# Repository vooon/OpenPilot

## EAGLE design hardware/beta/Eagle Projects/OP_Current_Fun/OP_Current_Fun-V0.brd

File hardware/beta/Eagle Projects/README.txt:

These are all easily accessible community projects, check schematic files for their usage licenses.

Extra or custom libraries are in lbr/Other.
OSH Park cam and DRU scripts are here as well.

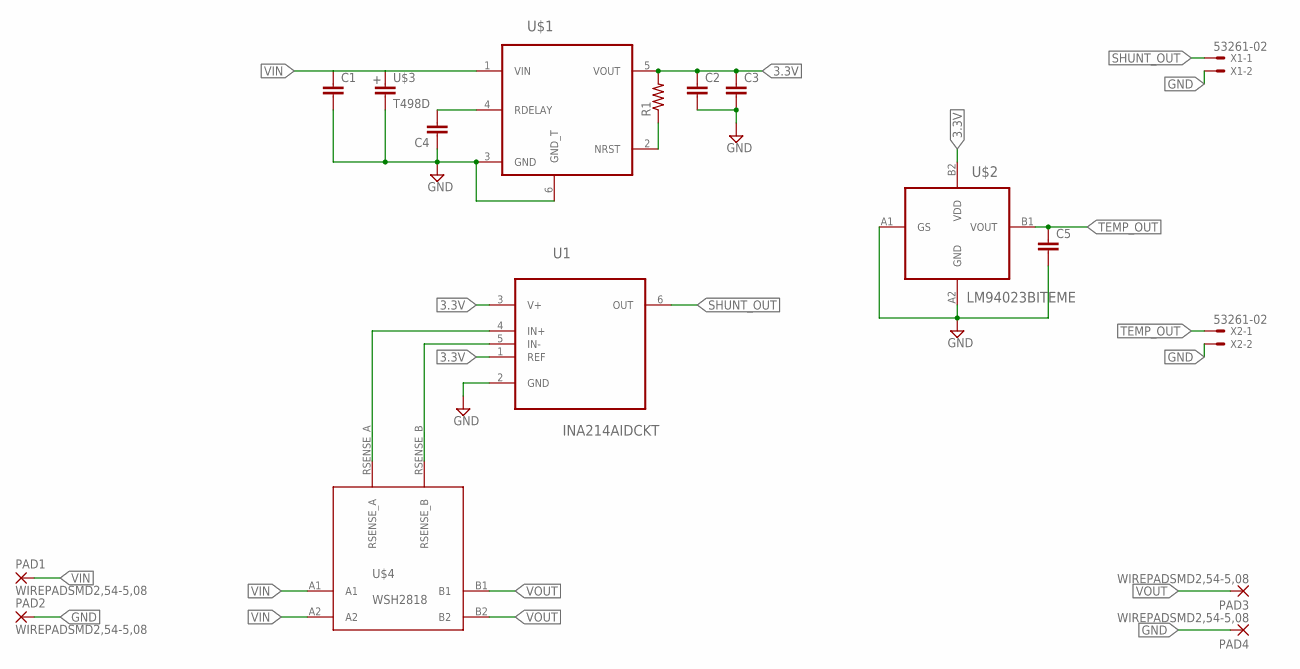
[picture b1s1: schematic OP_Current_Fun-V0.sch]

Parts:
C1, C2, C3, C5: C-EUC0603K; C0603K
C4: C-EUC0805K; C0805K
PAD1, PAD2, PAD3, PAD4: WIREPADSMD2,54-5,08; SMD2,54-5,08
R1: R-US_R0402; R0402
U1: INA214AIDCKT; SOT65P210X110-6N
U$1: TPS7A6033-Q1; TO-263-5
U$2: LM94023BITEME; BGA4C40P2X2_76X76X63
U$3: T498D; CT7343
U$4: WSH2818; 2818
X1, X2: 53261-02

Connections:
3.3V: C2.1, C3.1, R1.2, U1.1 (REF), U1.3 (V+), U$1.5 (VOUT), U$2.B2 (VDD)
GND: C1.2, C2.2, C3.2, C4.1, C5.2, PAD2.1, PAD4.1, U1.2 (GND), U$1.3 (GND), U$1.6 (GND_T), U$2.A1 (GS), U$2.A2 (GND), U$3.- (2), X1.2, X2.2
unnamed: U1.4 (IN+), U$4.RSENSE_A
unnamed: U1.5 (IN-), U$4.RSENSE_B
unnamed: C4.2, U$1.4 (RDELAY)
unnamed: R1.1, U$1.2 (NRST)
SHUNT_OUT: U1.6 (OUT), X1.1
TEMP_OUT: C5.1, U$2.B1 (VOUT), X2.1
VIN: C1.1, PAD1.1, U$1.1 (VIN), U$3.+ (1), U$4.A1, U$4.A2
VOUT: PAD3.1, U$4.B1, U$4.B2

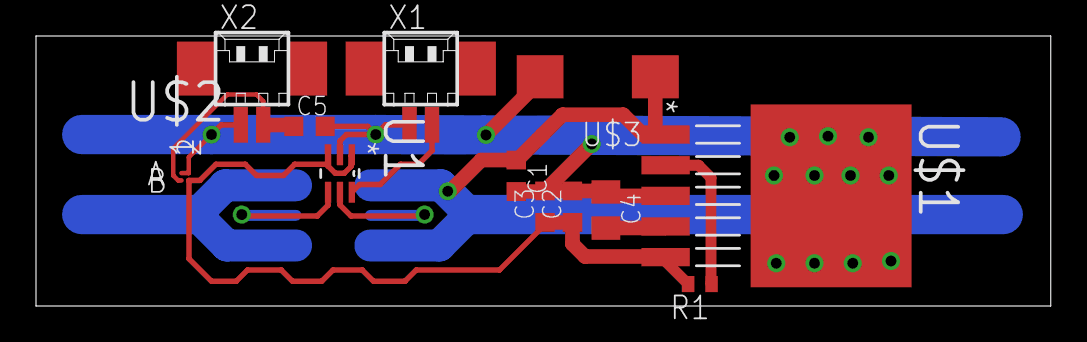
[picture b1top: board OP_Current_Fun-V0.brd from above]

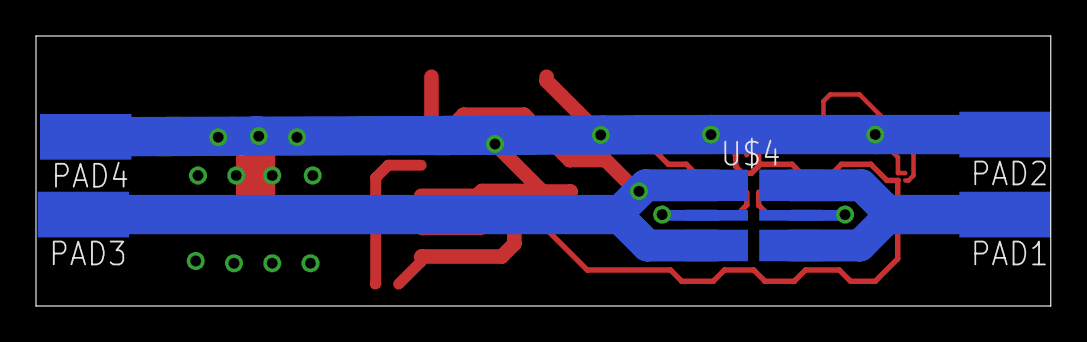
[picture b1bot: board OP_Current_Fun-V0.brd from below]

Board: 2 copper layers, 56.4 x 15.0 mm, 17 parts (5 on the bottom side), 10 nets.

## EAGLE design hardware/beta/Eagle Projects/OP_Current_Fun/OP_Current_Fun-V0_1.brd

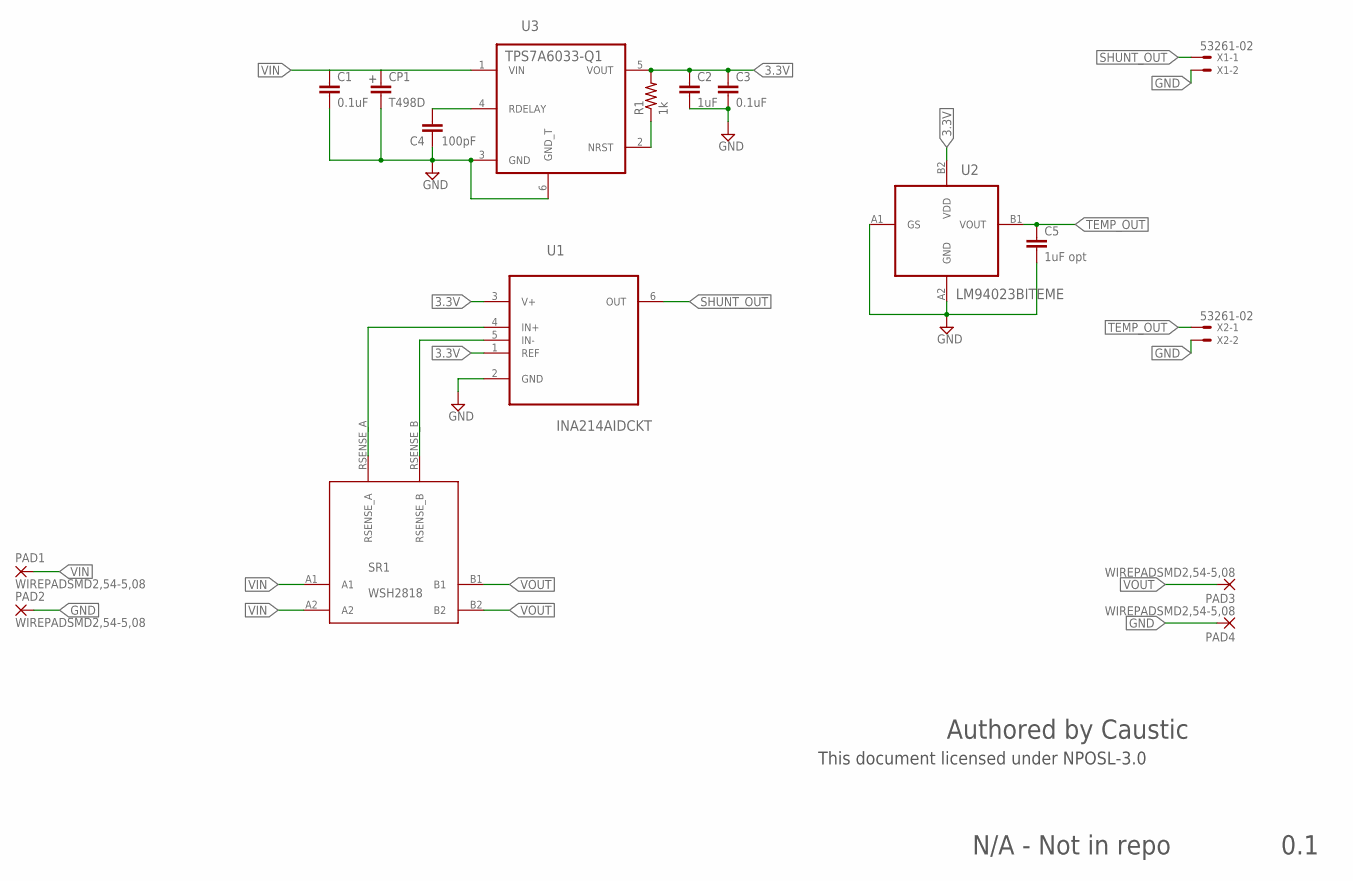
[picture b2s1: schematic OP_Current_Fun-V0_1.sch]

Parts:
C1, C3: 0.1uF; C0603K
C2: 1uF; C0603K
C4: 100pF; C0805K
C5: 1uF opt; C0603K
CP1: T498D; CT7343
PAD1, PAD2, PAD3, PAD4: WIREPADSMD2,54-5,08; SMD2,54-5,08
R1: 1k; R0402
SR1: WSH2818; 2818
U1: INA214AIDCKT; SOT65P210X110-6N
U2: LM94023BITEME; BGA4C40P2X2_76X76X63
U3: TPS7A6033-Q1; TO-263-5
X1, X2: 53261-02

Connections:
3.3V: C2.1, C3.1, R1.2, U1.1 (REF), U1.3 (V+), U2.B2 (VDD), U3.5 (VOUT)
GND: C1.2, C2.2, C3.2, C4.1, C5.2, CP1.- (2), PAD2.1, PAD4.1, U1.2 (GND), U2.A1 (GS), U2.A2 (GND), U3.3 (GND), U3.6 (GND_T), X1.2, X2.2
unnamed: SR1.RSENSE_A, U1.4 (IN+)
unnamed: SR1.RSENSE_B, U1.5 (IN-)
unnamed: C4.2, U3.4 (RDELAY)
unnamed: R1.1, U3.2 (NRST)
SHUNT_OUT: U1.6 (OUT), X1.1
TEMP_OUT: C5.1, U2.B1 (VOUT), X2.1
VIN: C1.1, CP1.+ (1), PAD1.1, SR1.A1, SR1.A2, U3.1 (VIN)
VOUT: PAD3.1, SR1.B1, SR1.B2

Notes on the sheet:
0.1
N/A - Not in repo
Authored by Caustic
This document licensed under NPOSL-3.0

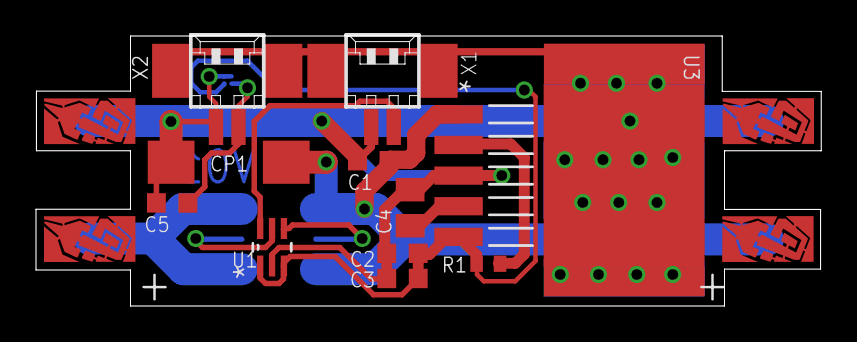
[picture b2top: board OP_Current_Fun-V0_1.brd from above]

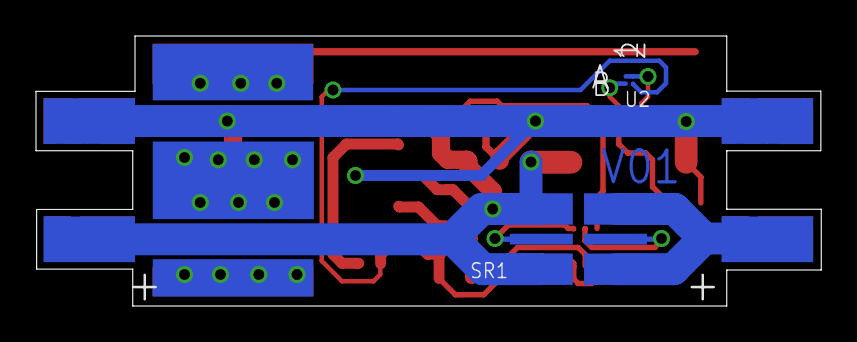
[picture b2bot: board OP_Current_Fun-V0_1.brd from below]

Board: 2 copper layers, 43.6 x 15.0 mm, 21 parts (6 on the bottom side), 10 nets.

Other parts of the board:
U$1, U$2, U$3, U$4: LOGO2,54X5,08PAD

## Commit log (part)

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2013-01-22 Added polarssl config include file.
2013-01-22 Fixed git submodule command.
2013-01-27 Added attitude direct control mode
    Attidude direct control mode is a regular pid control loop
    controlling a channel output to achieve an attitude. It works
    just like the Attutude mode except it is not a cascade controller.
    This is beneficial for controlling vehicles with reduced control over
    roll/pitch/yaw so that the cascade loop no longer makes sense (ie become
    impossible to tune)
2013-02-08 + added native Signals library
2013-02-08 + added classes: CApplication, CFile, CIODevice
2013-02-10 +added class: CStringList
2013-02-10 +added class CVariant
2013-02-21 Hitl fixes
2013-02-23 QT 5.0.1 *bugfixes *fix rawhid win event
2013-03-03 Updated arm toolchain filename. Updated to OP hosting URL (for 32bit).
2013-03-04 Copy over inc from CopterControl
2013-03-05 Copy coptercontrol main.c over
2013-03-05 Small Makefile comment to self
2013-03-05 Added CCUniversal to Makefile so we can try to build the bootloader
2013-03-05 Copied over board hw defs
2013-03-05 Created the External Library folder and readme.
2013-03-05 Stripped down the Standard Periph Libraries, do not need examples
2013-03-05 Start of MCU specific breakout and test, successful build
2013-03-06 Most of the versioned std lib works. The stdlib in PiOS is a different version, will have to patch or detect to maintain compatibility.
2013-03-07 Removed struct consts from bard_hw_defs
2013-03-07 Removed const from pios_board for led_cfg
2013-03-07 Removed const from first part of pios_usb
2013-03-08 Note to self about code duplication
2013-03-08 Updated F103 board file to versioned stdPeriphLib
2013-03-08 PiOS_led_priv converted to preprocessor test
2013-03-08 Converted PiOS_board to preprocessor test
2013-03-08 Added the filename stub needed to deal with the StdPeriphLib irregularity. Now builds as it should.
2013-03-08 Updated TESTNAME to pull in the F30x board file
2013-03-08 Copied over linker files, seem to match
2013-03-13 Added OP_Current_Fun and associated Eagle elements
2013-03-17 Remove discontinued AHRS files
2013-03-17 pios: common PIOS header guards
2013-03-17 pios: STM32F10x PIOS #ifdef guards
2013-03-17 Makefile: indents, comments, spacing, $(CMDS) variables, etc.
    How to invoke external command instead of shell builtin on Windows:
    ECHO := /bin/echo
2013-03-17 Makefile: use exported variables in firmware-defs.mk
    Note that $(QUOTE) variable is uppercased. Windows make does not
    export lowercased variables with export keyword (even if must do).
2013-03-17 Makefile: firmware makefiles cleanup (CC)
2013-03-17 Makefile: fix some MODULE_Name_BUILTIN checks and Makefile
    These names are automatically generated by make using the list
    of mandatory (always started) modules. Wrong names mean they can
    be disabled, fixed now.
2013-03-17 Makefile and pios_config.h cleanup for PipXtreme
    Now PipXtreme uses the same apps-defs.mk file as CopterControl.
    Next steps are F4 boards.
2013-03-17 Remove (almost) exact copy of dosfs from F1-specific directory
    The difference was in dfs_sdcard.c, line 107:
    -if((status = PIOS_SDCARD_SectorRead(sector, buffer)) < 0) {
    +if((status = PIOS_SDCARD_SectorRead(sector, buffer)) != 0) {
    Currenly unused, kept as is.
2013-03-17 Makefile: add --warn-common and --fatal-warnings to identify name clashes
    This will stop builds if few same symbols are found when linking.
    It should not be the case, but possible and may give unpredicted results.
2013-03-17 Remove duplicated global var and defines from board definition file
    Was caught using just added linker options:
    LDFLAGS += -Wl,--warn-common
    LDFLAGS += -Wl,--fatal-warnings
2013-03-17 pios_debug: use PIOS_INCLUDE_DEBUG_CONSOLE to DEBUG_PRINTF(level, ...)
    Inconsistent use of debug macros in board definition files resulted in
    BU compilation error. It was attempted to use PIOS_COM_SendFormattedStringNonBlocking()
    directly even if PIOS_COM was not included (like for BootloaderUpdater).
    So this function in pios_debug.c was replaced by DEBUG_PRINTF() macro.
    The macro itself is defined in pios_debug.h file. Its definitions are
    removed from board files. And to use it one has to define in pios_config.h:
2013-03-17 Remove never used op_config.h files (all occurences were empty)
2013-03-17 pios: add more global config options used by Revo
2013-03-17 pios_bl_helper.h: why all these empty lines?
2013-03-17 Makefile: better options sequence in common-defs.mk
2013-03-17 Makefile: rework RevoMini Makefile to use new make system
2013-03-17 Move 3rd party printf formatter functions from PiOS to Libraries folder
    They are not a PiOS, but 3rd party libraries. They even should not
    be placed to the same (PiOS) library directory due to the printf symbol
    clashes (if all *.c from the folder are built). So they are moved, and
    each target can include that one which is necessary/desired.
2013-03-17 *.mk: fix double '/' in path names ($dir always returns it as a last char)
    Also minor formatting of all library.mk files.
2013-03-18 Updated Makefile to use MCUDENSITY
2013-03-19 Introduced CMSIS_Rules as this is different for each, repaired new device detection, added first have of CMSIS link-in
2013-03-19 Coppied over Legacy DSP CMSIS2 (?) library that was being used and does not exist in the current F10x due to no DSP module
2013-03-19 Linked in Legacy USB Driver
2013-03-19 Strange TRUE-FALSE issue workaround using a project define. Do not know if this is a new CMSIS issue or not.
2013-03-19 Corrected the explicit CMSIS c file pull in, Now builds the F103 bootloader.
2013-03-19 Added versioned USB and DSPLib libraries for F10x
2013-03-19 New USB uses hw_config.h, setting up a copy and compile-time patch method
2013-03-19 Makefile: swap some lines for readability, no real code changes
2013-03-19 Makefile: update help output
2013-03-19 Minor cleanup of .gitignore file
2013-03-22 start DiscoveryF4 based branch revomini
    SPI flash 25P16VP and RFM22b:
    FLASH MOSI -> SPI2_MOSI (PB15)
    FLASH MISO -> SPI2_MISO (PB14)
    FLASH SCK -> SPI2_SCK (PB13)
    FLASH CS -> SPI2_NSS (PB12)
    RFM22b CS -> GPIO_OUT (PD10)
2013-03-23 Packaging: move common part into the top Makefile
    This includes all dependencies and generates package directory
    with renamed firmware files.
2013-03-23 Posix compile-only fix (still needs a lot of rework)
    This is a patch to make simposix buildable. It does not use new
    makefiles and should be reworked.
2013-03-24 Guidance fixes, Autoland test
2013-03-29 update protocols, telemetry test
2013-04-05 Added notes and method to pass TARGET_MCU= to the bootloader build
2013-04-05 Partial patch, not working
2013-04-05 Forgot to stage the second patch file with the last commit
2013-04-05 Patch make loop is working for the first one only
2013-04-05 Correctly assign VAR to their inetent for the loop
2013-04-05 Patch reversal is working beautifully
2013-04-05 Removed working test code for clean and patch handling
2013-04-05 Comments regarding functionality change in the Makefiles
2013-04-05 Patching for const in usb_core.h structure for PiOS compatability
2013-04-05 Removed CopyInRoutine const, maybe I can chase out the USB problem
2013-04-06 Large non-const changes to PiOS USB, maybe they will fix the USB problem
2013-04-06 Test for automatic EOL conversion. Still actual changes and should be merged
2013-04-07 Small changes in prep for F303 bootloader build
2013-04-11 First part of hw def adaption for CC3DF3
2013-04-11 First part of GPIOA converted
2013-04-11 Port GPIO for F3, upto line 870ish
2013-04-11 F3 GPIO port 1318
2013-04-12 Changed all references to PipXtreme on flight side to OPLink.
2013-04-12 OP-896: Linux and Mac are case-sensitive
2013-04-13 OP-914: Additional cleanup of the RFM22B driver code. Updated to code to the current coding standard. Added Doxygen documentation. Rearranged functions into functional groups to simplify reading the 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
2013-04-14 OP-896: remove old board configs (ESC, INS, OpenPilot)
2013-04-14 OP-896: rename RevoMini to Revolution
2013-04-16 OP-914 - Converted PIOS_RFM22B_Validate back into a normal function from an inline.
2013-04-16 +[uavobjectgenerator] added generator for native code
2013-04-16 +added native telemetry
2013-04-18 Changed GPIO IMU to IN and PuPd_DOWN for USB initialization
2013-04-18 Updated PinRemapConfig to PinAFConfig. Issues may arise as the new one is pin specific, not port usage wide.
2013-04-19 Added tamper pin remap for F3
2013-04-19 Correct device
2013-04-21 USB const round 2 issue, pragma bypass to compare actual consumption
2013-04-22 Hopefully finished the F3 USB port for hook
2013-04-22 Added some version test for locations and linker naming changes
2013-04-23 new version
2013-04-28 OP-924: Completely turn off PPM output when it's not being refreshed. Also fixed testing of PPM input on the OPlink that was broken when the return values were changed to negative values. The PPM val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
2013-04-28 OP-924: Ensures that the PPM pulse turns off between PPM frames.
2013-05-04 OP-922: DEBUG=YES
    Put back default value for DEBUG option to NO.
2013-05-06 forgot one
2013-05-09 Makefile TargetMcu support
2013-05-09 Added FreeRTOS V7.4.2 to ExtLibs, less the Demo Directories
2013-05-09 Added path inheritance for RTOS
2013-05-09 Added CMSIS detection and path correction
2013-05-09 Added Extra CMSIS detection for path issue
2013-05-09 LDFLAG detection for stdperiph compatibility change
2013-05-10 The F3 needs the rcc header for timers
2013-05-10 Pushed portable FreeRTOS compiler selection to the mcu-board file
2013-05-12 Pin port for F3
2013-05-13 SWD new AF remap method for F3
2013-05-14 Repair case messup
2013-05-15 Adds setting HSE_VALUE on all F1 targets (should only be necessary if the HSE clock is not 8MHz).
2013-05-16 Splits PIOS_Sys_Init into a function that calls SystemInit, and another function (PIOS_SYS_Init_No_CMSIS_Init) that performs the rest of the initialization. This allows calling just the second functi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
2013-05-17 Reverted change to pios_sys.h
2013-05-22 unrustify
2013-05-25 Add uninstall icon to windows package.
    Yes, I really am commiting this one line fix so bamboo builds it for me <3
    Bamboo
2013-05-25 Added rest of fields to the uninstall section of the NSIS installer, minor polish work.
2013-05-25 fix serialport settings and optionpages, no more crashing when missing defaults
2013-05-26 Windows release fixes
2013-05-27 - changex from px to pt, some compile trouble on windows
2013-06-02 OP-985 Changes the master clock scaling on OPLinkMini and CC3D to 10, to produce a master clock of 80MHz. Unfortunately, this makes USB unreliable. USB requires a master clock of either 48 or 72 MHz.
2013-06-14 qt5 win usb fix
2013-06-16 increased the size of the temporary dmg file
2013-06-16 removed unnecessary copying of libraries
2013-06-16 fixed error build file of dmg
2013-06-18 Removes several of the air datarate settings, and fine tunes the calculation of the max packet length from the datarate and packet time. 9600, 19200, 36400, and 57600 modes tested. Tested 19200 in on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
2013-06-18 OP-932 Adds claiming of the SPI bus in the OPLink channel change function.
2013-06-22 qt5.1.0-rc1 linux fixes
2013-06-23 Fix windows hid connection failure if board was already connected and gcs started. Was getting sharing violation error.
2013-06-23 OP-932 Adds a semaphore to PPM input to signal when a new frame has been received. This can be used to process a new frame with as low a latency as possible.
2013-06-23 OP-932 Adds working one-way mode to the OPLink radio connection. In this mode, packets will only flow from the ground side (coordinator modem) to the flight side modem.
2013-06-23 OP-932 A significant re-work of the OPLink and configuration of the OPLink. Auto-configuration is removed, and remote modems are bound the coordinator, rather than the other way around. Timing of the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
2013-06-27 UPdated CREDITS.TXT
2013-07-04 ROS GW: fix toStringData()
2013-07-06 ROS GW: fix array comma
2013-07-12 Adds support for MPU6050 I2C interface to MPU6000 driver. Also adds a function for reading sensors from the register, rather than reading from the FIFO. Turns off the FIFO for all MPU6000 boards.
2013-07-14 Splits out SPI ad I2C interface functions into separate files.
2013-07-15 OP-1039: Fixed mpu6000 scaling on CC3D.
2013-07-20 ROS GW: fix toStrringData() code generation
2013-07-27 OP-1039: Moves changing of the SPI bus speed into the ClaimBus call for all SetReg calls in the mpu6000 driver. This ensures that the bus is slowed when the registers are set, and and it also ensures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
2013-07-28 OP-1039: Uses a structure to access sensor data rather than local variables.
2013-07-31 uncrustify, keep the table formatted
2013-08-03 DiscoveryF4: inital port using revolution as a source.
    Builds well, but currently don't work.
    BL do not transfer to DFU mode, FW crashes on init.
